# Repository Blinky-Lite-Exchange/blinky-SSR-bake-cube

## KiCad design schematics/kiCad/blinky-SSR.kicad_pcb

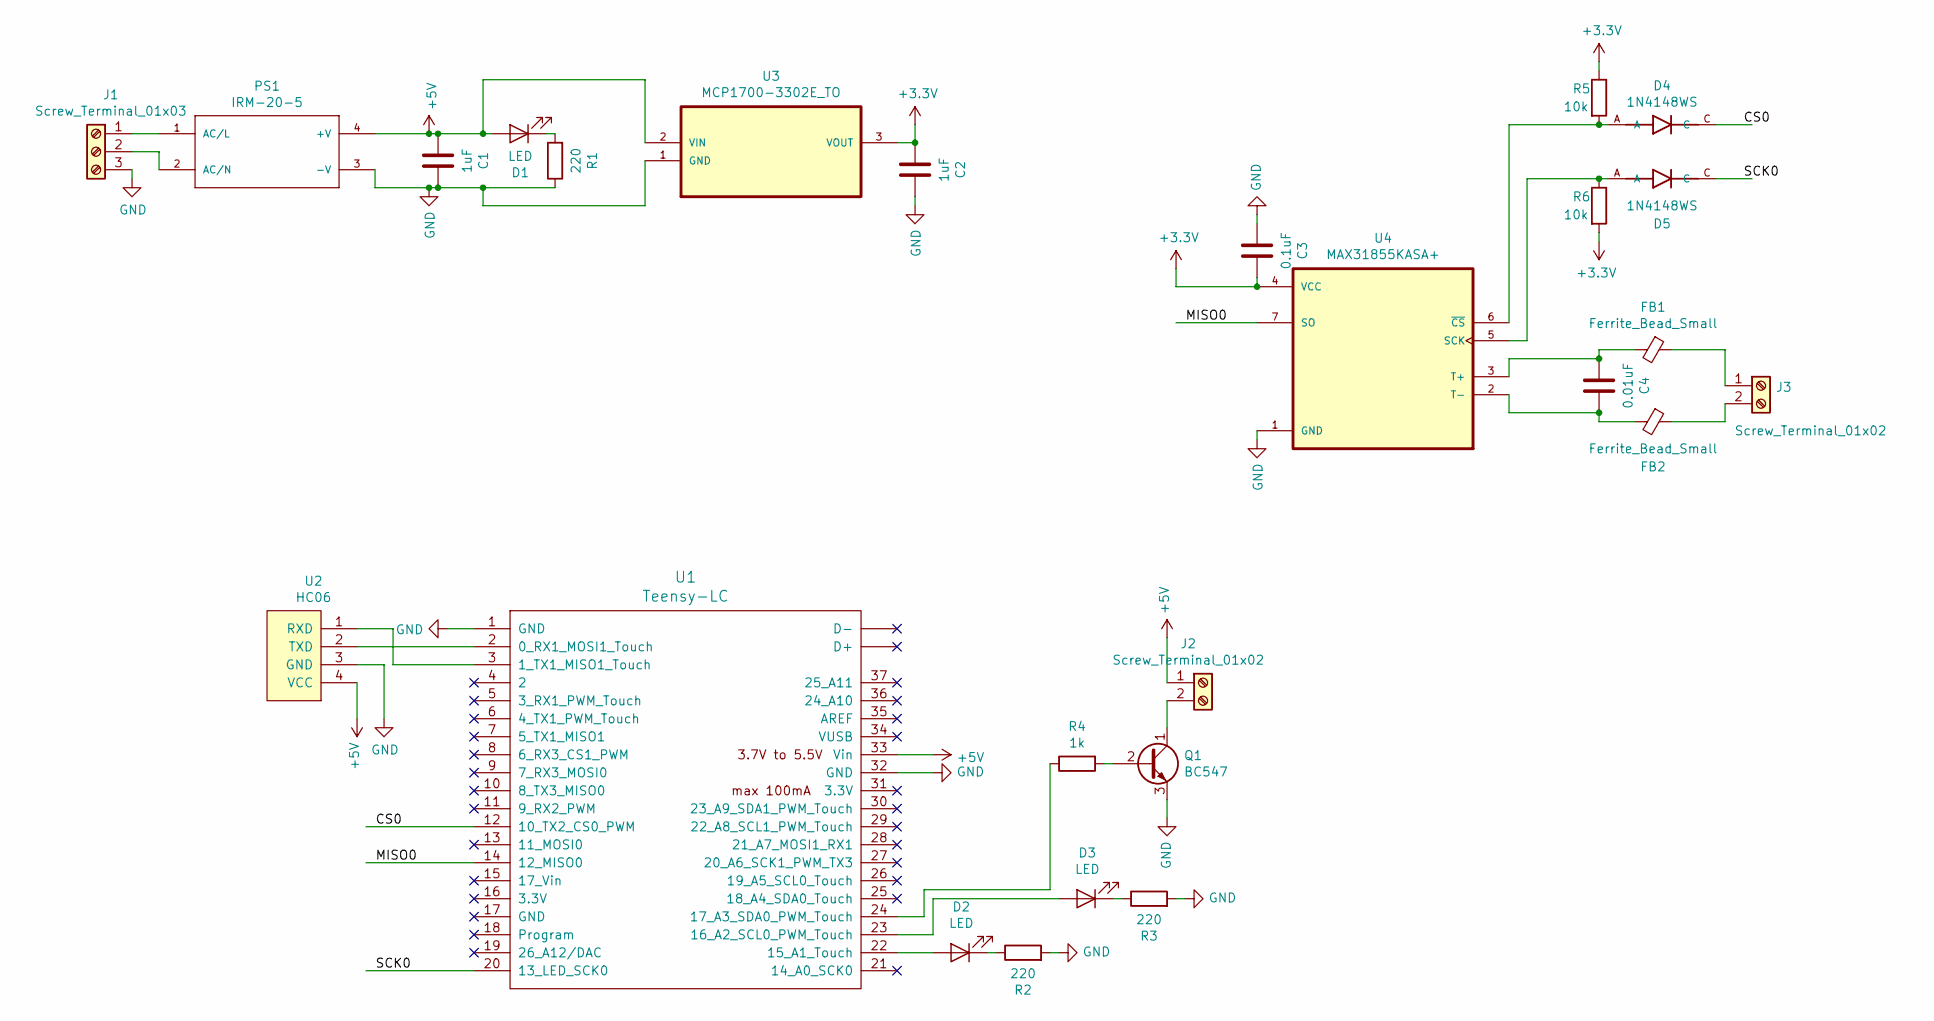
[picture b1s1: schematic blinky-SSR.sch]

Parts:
C1, C2: 1uF; C_1206_3216Metric_Pad1.42x1.75mm_HandSolder
C3: 0.1uF; C_1206_3216Metric_Pad1.42x1.75mm_HandSolder
C4: 0.01uF; C_1206_3216Metric_Pad1.42x1.75mm_HandSolder
D1, D2, D3: LED; LED_D5.0mm
D4, D5: 1N4148WS; SODFL2512X100N
FB1, FB2: Ferrite_Bead_Small; L_1206_3216Metric_Pad1.42x1.75mm_HandSolder
J1: Screw_Terminal_01x03; TerminalBlock_bornier-3_P5.08mm
J2, J3: Screw_Terminal_01x02; TerminalBlock_bornier-2_P5.08mm
PS1: IRM-20-5; CONV_IRM-20-5
Q1: BC547; TO-92_Inline_Wide
R1, R2, R3: 220; R_1206_3216Metric_Pad1.42x1.75mm_HandSolder
R4: 1k; R_1206_3216Metric_Pad1.42x1.75mm_HandSolder
R5, R6: 10k; R_1206_3216Metric_Pad1.42x1.75mm_HandSolder
U1: Teensy-LC; Teensy30_31_32_LC
U2: HC06
U3: MCP1700-3302E_TO; TO127P254X495-3; MPN MCP1700-3302E/TO
U4: MAX31855KASA+; SOIC127P600X175-8N

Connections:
+3V3: C2.2, C3.1, R5.1, R6.2, U3.3 (VOUT), U4.4 (VCC)
+5V: C1.2, D1.2 (A), J2.1, PS1.4 (+V), U1.33 (Vin), U2.4 (VCC), U3.2 (VIN)
/CS0: D4.C, U1.12 (10_TX2_CS0_PWM)
/MISO0: U1.14 (12_MISO0), U4.7 (SO)
/SCK0: D5.C, U1.20 (13_LED_SCK0)
GND: C1.1, C2.1, C3.2, J1.3, PS1.3 (-V), Q1.3 (E), R1.1, R2.2, R3.2, U1.1 (GND), U1.32 (GND), U2.3 (GND), U3.1 (GND), U4.1 (GND)
unnamed: C4.1, FB2.2, U4.2 (T-)
unnamed: C4.2, FB1.2, U4.3 (T+)
unnamed: D1.1 (K), R1.2
unnamed: D2.1 (K), R2.1
unnamed: D2.2 (A), U1.22 (15_A1_Touch)
unnamed: D3.1 (K), R3.1
unnamed: D3.2 (A), U1.23 (16_A2_SCL0_PWM_Touch)
unnamed: D4.A, R5.2, U4.6 (~CS)
unnamed: D5.A, R6.1, U4.5 (SCK)
unnamed: FB1.1, J3.1
unnamed: FB2.1, J3.2
unnamed: J1.1, PS1.1 (AC/L)
unnamed: J1.2, PS1.2 (AC/N)
unnamed: J2.2, Q1.1 (C)
unnamed: Q1.2 (B), R4.2
unnamed: R4.1, U1.24 (17_A3_SDA0_PWM_Touch)
unnamed: U1.2 (0_RX1_MOSI1_Touch), U2.2 (TXD)
unnamed: U1.3 (1_TX1_MISO1_Touch), U2.1 (RXD)

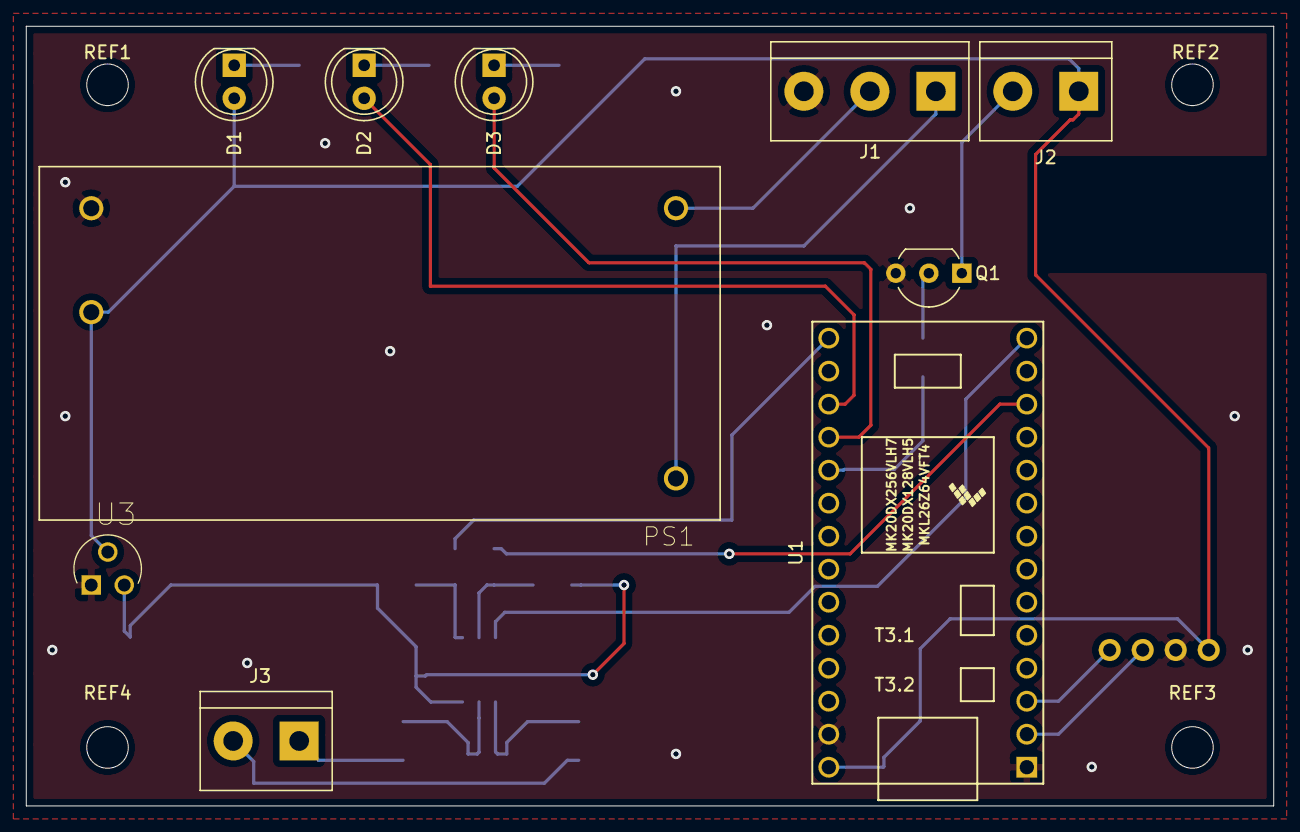
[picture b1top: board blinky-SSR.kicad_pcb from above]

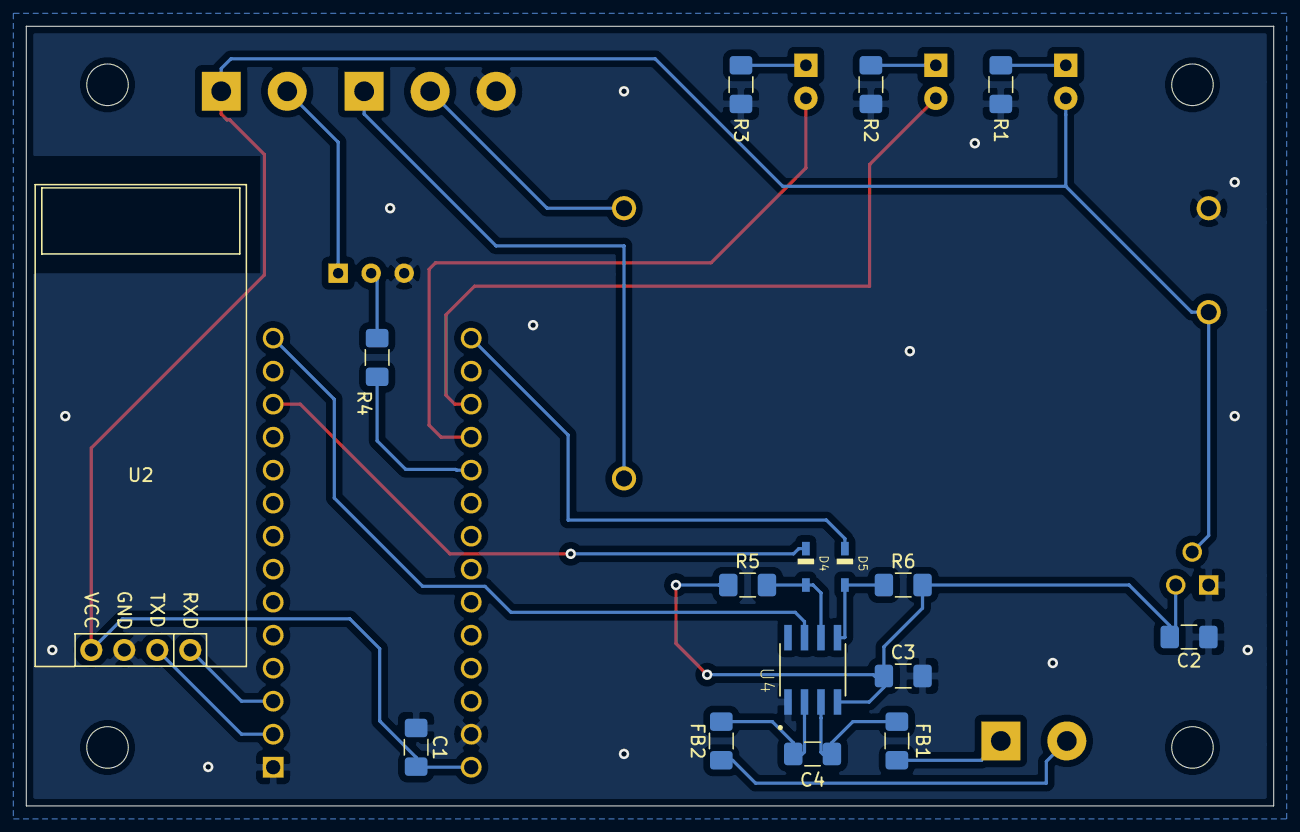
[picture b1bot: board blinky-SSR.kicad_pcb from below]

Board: 2 copper layers, 96.0 x 60.0 mm, 30 parts (16 on the bottom side), 24 nets.

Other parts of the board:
REF1, REF2, REF3, REF4: MountingHole_3.2mm_M3

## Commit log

2021-01-25 circuit designed
2021-02-08 changed project name
2021-02-16 working cube software
2021-02-25 added duty factor set
2021-03-28 bluetooth com check
2022-03-01 added blinky-bus
2022-03-03 changed duty factor readback to percent
